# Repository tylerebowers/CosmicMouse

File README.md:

# Cosmic Mouse

This is 6DOF mouse for CAD, inspired by the Space Mouse by 3DConexion, it uses 3x 3D Hall effect sensors over I2C with a custom single-piece isotropic spring which floats the knob in space. Firmware compensates for magnetic cross-talk by using a physics-based magnetic dipole model and the Levenberg-Marquardt algorithm to iteratively solve for the knob's pose by minimizing the difference between measured and predicted magnetic fields (see firmware/model.md). The enclosure knob, and diffuser are resin printed vis MSLA for smoothness. The knob shaft is printed in PETG and sping in TPU. I also used a steel base weight and non-slip silicone pad to keep it planted during movements. This project is sponsored by [PCBWay](https://www.pcbway.com/).

The Cosmic Mouse is *likely capable* of emulating a real Space Mouse... On an unrelated note, you should see firmware/src/config.h for some random funny strings. 

The design process post can be seen on my website [here](https://tylerebowers.com/posts/cosmic_mouse). I am working on a Youtube video.

### Working Model:

### Cross Section:

### PCB:

### Isotropic Spring:

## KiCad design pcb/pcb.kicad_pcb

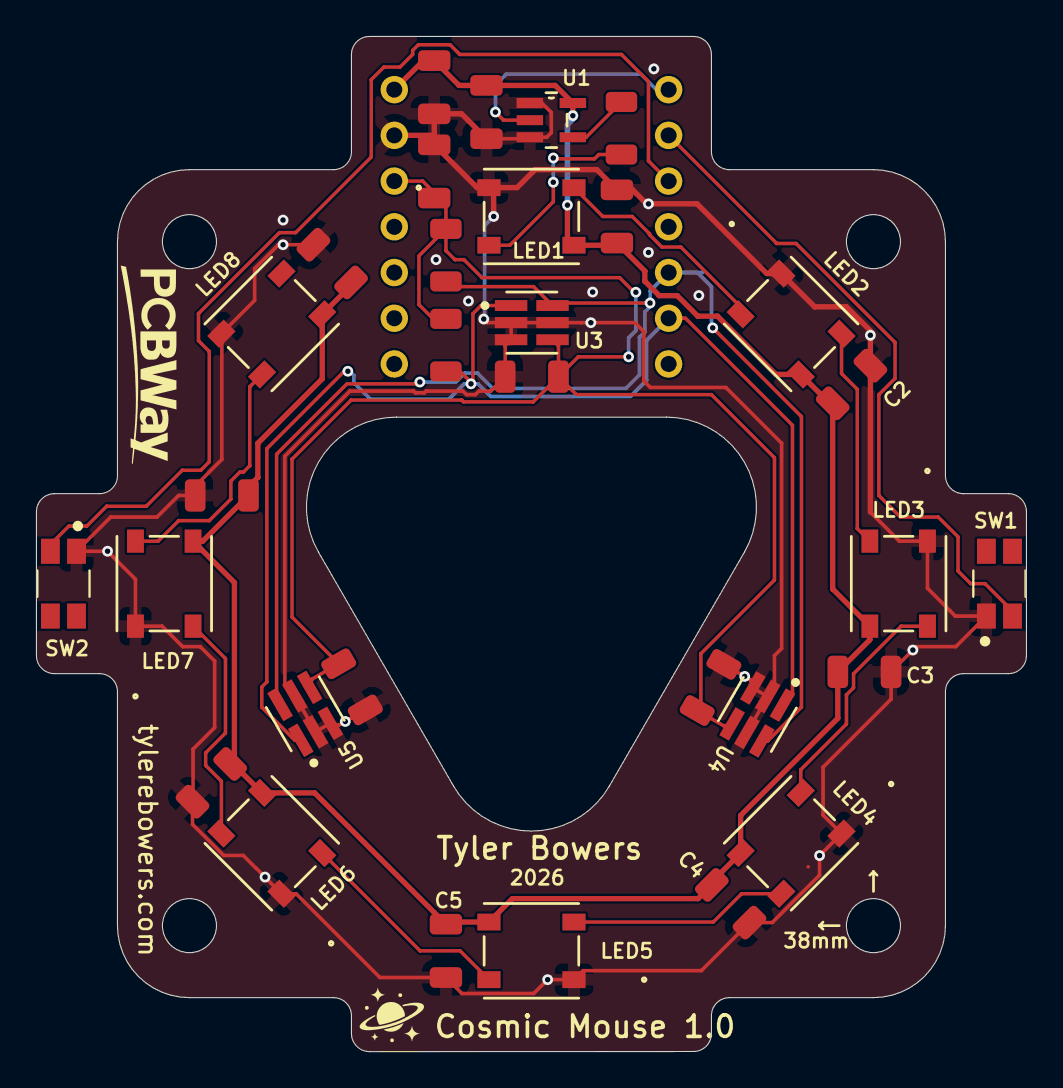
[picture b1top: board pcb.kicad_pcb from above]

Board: 2 copper layers, 55.0 x 56.4 mm, 32 parts (1 on the bottom side), 17 nets.

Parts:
C1, C2, C3, C4, C5, C6, C7, C8, C9, C10, C11, C12, C13, C14: C_1206_3216Metric; C_1206
LED1, LED2, LED3, LED4, LED5, LED6, LED7, LED8: LED_IN-PI55TAT_INL
R1, R2, R3: R_1206_3216Metric; R_1206
SW1, SW2: SW_EVQ-P7J01P
U1: DBV5
U2: XIAO-RP2350-DIP
U3, U4, U5: DBV0006A-IPC_A

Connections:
+3.3V: C10.2, C11.2, C12.2, C14.2, R1.2, R2.2, U2.12, U3.4, U4.4, U5.4
+5V: C1.1, C2.1, C3.1, C4.1, C5.1, C6.1, C7.1, C8.1, C9.1, C13.1, LED1.4, LED2.4, LED3.4, LED4.4, LED5.4, LED6.4, LED7.4, LED8.4, U1.5, U2.14
D1_mc: SW1.2_1, U2.2
D2_mc: SW2.2_1, U2.3
GND: C1.2, C2.2, C3.2, C4.2, C5.2, C6.2, C7.2, C8.2, C9.2, C10.1, C11.1, C12.1, C13.2, C14.1, LED1.1, LED2.1, LED3.1, LED4.1, LED5.1, LED6.1, LED7.1, LED8.1, SW1.1_1, SW2.1_1, U1.1, U1.3, U2.13, U3.2, U3.3, U3.5, U4.2, U4.3, U4.5, U5.2, U5.3, U5.5
unnamed: LED1.3, R3.1
unnamed: LED1.2, LED2.3
unnamed: LED2.2, LED3.3
unnamed: LED3.2, LED4.3
unnamed: LED4.2, LED5.3
unnamed: LED5.2, LED6.3
unnamed: LED6.2, LED7.3
unnamed: LED7.2, LED8.3
unnamed: U1.2, U2.1
unnamed: R3.2, U1.4
unnamed: R1.1, U2.5, U3.6, U4.6, U5.6
unnamed: R2.1, U2.6, U3.1, U4.1, U5.1

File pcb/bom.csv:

"Reference","Qty","Value","Footprint","Datasheet"
"C1,C2,C3,C4,C5,C6,C7,C8,C10,C11,C12,C13","12","100nf","PCM_JLCPCB:C_1206",""
"C9,C14","2","10uf","PCM_JLCPCB:C_1206",""
"LED1,LED2,LED3,LED4,LED5,LED6,LED7,LED8","8","IN-PI55TATPRPGPB","space_mouse:LED_IN-PI55TAT_INL","IN-PI55TATPRPGPB"
"R1,R2","2","4.7k","PCM_JLCPCB:R_1206",""
"R3","1","220","PCM_JLCPCB:R_1206",""
"SW1,SW2","2","EVQ-P7J01P","space_mouse:SW_EVQ-P7J01P",""
"U1","1","SN74AHCT1G125DBVR","space_mouse:DBV5","https://www.ti.com/lit/gpn/sn74ahct1g125"
"U2","1","XIAO-RP2350-DIP","Seeed_Studio_XIAO_Series:XIAO-RP2350-DIP",""
"U3","1","TMAG5273A1QDBVR","space_mouse:DBV0006A-IPC_A","https://www.ti.com/lit/gpn/tmag5273"
"U4","1","TMAG5273B1QDBVR","space_mouse:DBV0006A-IPC_A","https://www.ti.com/lit/gpn/tmag5273"
"U5","1","TMAG5273C1QDBVR","space_mouse:DBV0006A-IPC_A","https://www.ti.com/lit/gpn/tmag5273"
